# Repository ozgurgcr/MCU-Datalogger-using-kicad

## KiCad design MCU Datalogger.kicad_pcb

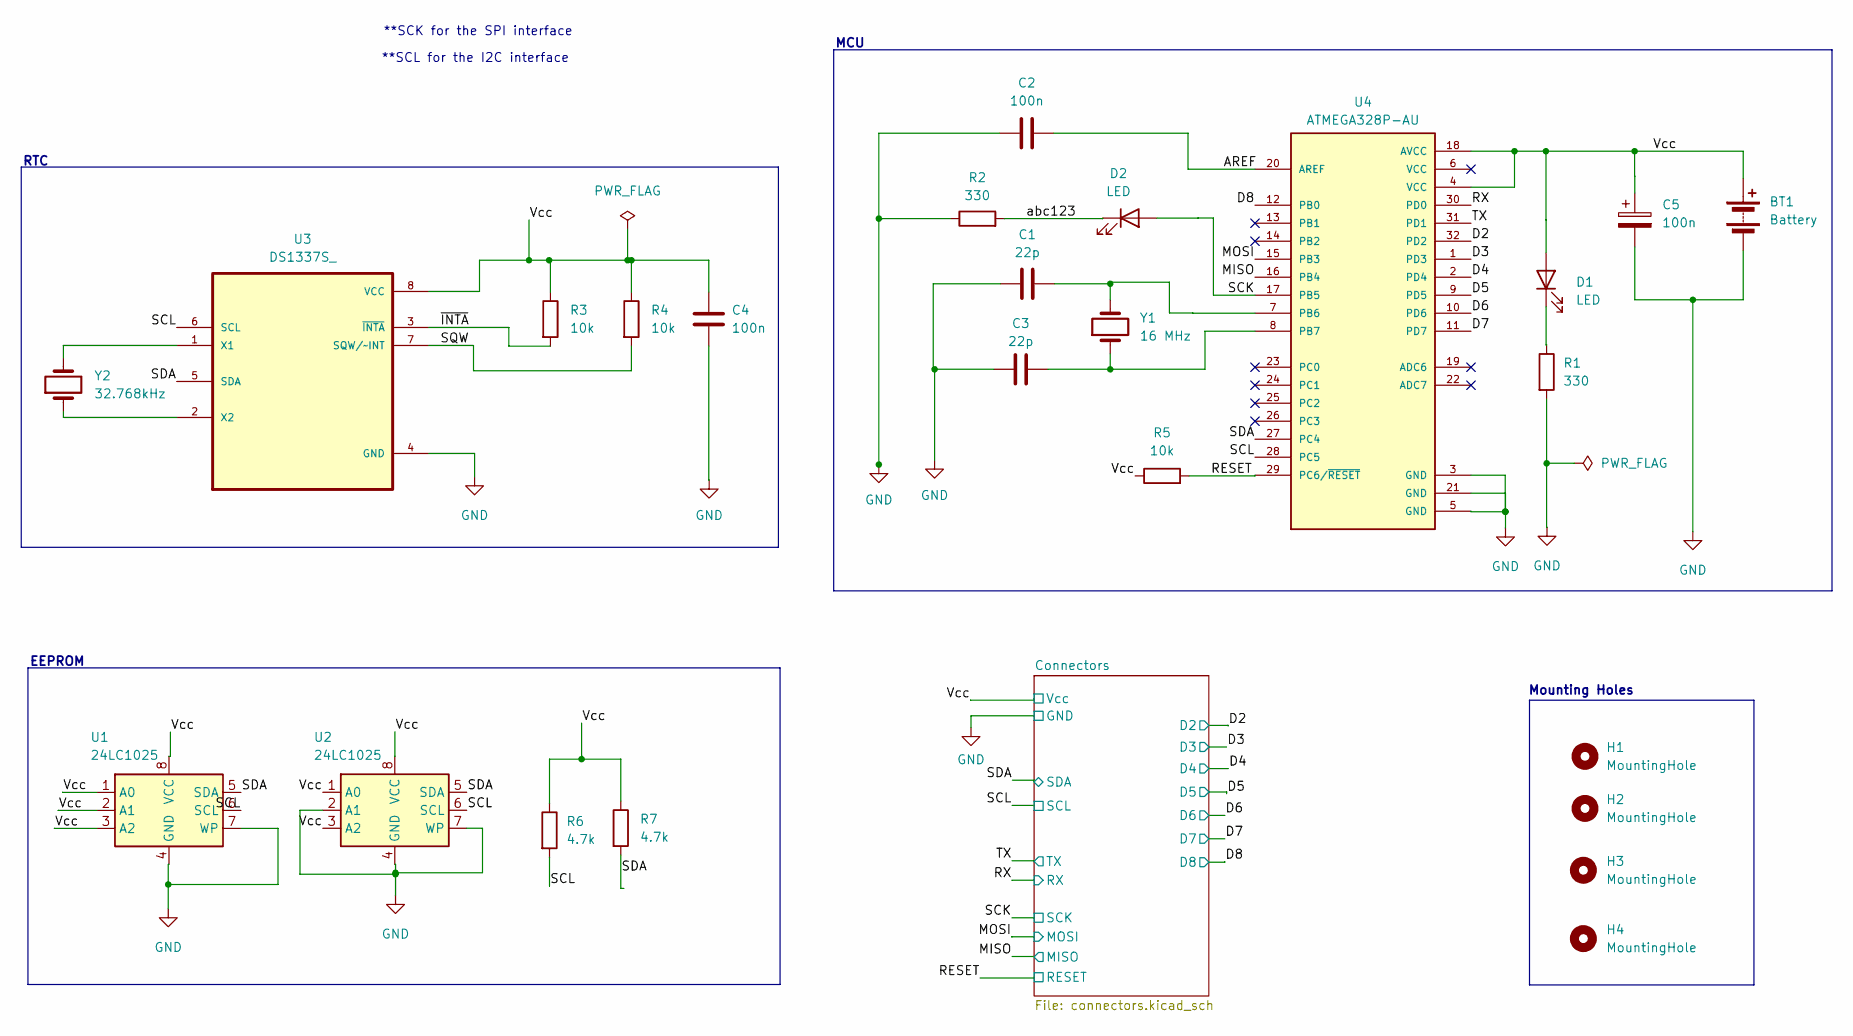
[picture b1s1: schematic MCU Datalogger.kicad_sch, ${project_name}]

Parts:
BT1: Battery; PinHeader_1x02_P2.54mm_Vertical
C1, C3: 22p; C_0805_2012Metric
C2, C4, C5: 100n; C_0805_2012Metric
D1, D2: LED; LED_0805_2012Metric
H1, H2, H3, H4: MountingHole; MountingHole_2.1mm
R1, R2: 330; R_0805_2012Metric
R3, R4, R5: 10k; R_0805_2012Metric
R6, R7: 4.7k; R_0805_2012Metric
U1, U2: 24LC1025; SOIC-8_5.23x5.23mm_P1.27mm
U3: DS1337S_; SOIC127P600X175-8N
U4: ATMEGA328P-AU; QFP80P900X900X120-32N; PARTREV 8271A
Y1: 16 MHz; Crystal_SMD_5032-2Pin_5.0x3.2mm_HandSoldering
Y2: 32.768kHz; Crystal_SMD_5032-2Pin_5.0x3.2mm_HandSoldering

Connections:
/AREF: C2.2, U4.20 (AREF)
/D2: U4.32 (PD2); also elsewhere on the board
/D3: U4.1 (PD3); also elsewhere on the board
/D4: U4.2 (PD4); also elsewhere on the board
/D5: U4.9 (PD5); also elsewhere on the board
/D6: U4.10 (PD6); also elsewhere on the board
/D7: U4.11 (PD7); also elsewhere on the board
/D8: U4.12 (PB0); also elsewhere on the board
/MISO: U4.16 (PB4); also elsewhere on the board
/MOSI: U4.15 (PB3); also elsewhere on the board
/RESET: R5.2, U4.29 (PC6/~RESET); also elsewhere on the board
/RX: U4.30 (PD0); also elsewhere on the board
/SCK: D2.2 (A), U4.17 (PB5); also elsewhere on the board
/SCL: R6.2, U1.6 (SCL), U2.6 (SCL), U3.6 (SCL), U4.28 (PC5); also elsewhere on the board
/SDA: R7.2, U1.5 (SDA), U2.5 (SDA), U3.5 (SDA), U4.27 (PC4); also elsewhere on the board
/SQW: R4.2, U3.7 (SQW/~INT)
/TX: U4.31 (PD1); also elsewhere on the board
/Vcc: BT1.1 (+), C4.2, C5.1, D1.2 (A), R3.1, R4.1, R5.1, R6.1, R7.1, U1.1 (A0), U1.2 (A1), U1.3 (A2), U1.8 (VCC), U2.1 (A0), U2.3 (A2), U2.8 (VCC), U3.8 (VCC), U4.4 (VCC), U4.18 (AVCC); also elsewhere on the board
/abc123: D2.1 (K), R2.2
/~INTA: R3.2, U3.3 (~INTA)
GND: BT1.2 (-), C1.1, C2.1, C3.1, C4.1, C5.2, R1.2, R2.1, U1.4 (GND), U1.7 (WP), U2.2 (A1), U2.4 (GND), U2.7 (WP), U3.4 (GND), U4.3 (GND), U4.5 (GND), U4.21 (GND); also elsewhere on the board
unnamed: D1.1 (K), R1.1
unnamed: U3.1 (X1), Y2.2
unnamed: U3.2 (X2), Y2.1
unnamed: C1.2, U4.7 (PB6), Y1.2
unnamed: C3.2, U4.8 (PB7), Y1.1

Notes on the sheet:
MCU
**SCL for the I2C interface
RTC
**SCK for the SPI interface
EEPROM
Mounting Holes

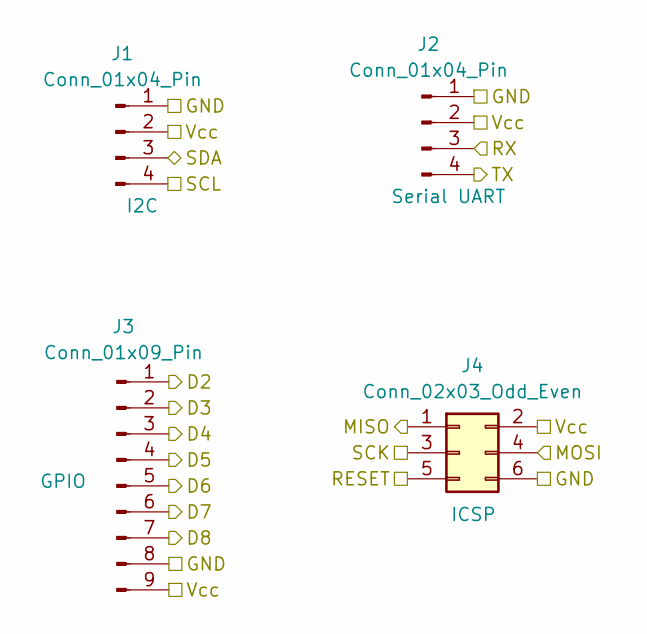
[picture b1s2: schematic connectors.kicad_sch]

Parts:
J1, J2: Conn_01x04_Pin; PinHeader_1x04_P2.54mm_Vertical
J3: Conn_01x09_Pin; PinHeader_1x09_P2.54mm_Vertical
J4: Conn_02x03_Odd_Even; PinHeader_2x03_P2.54mm_Vertical

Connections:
/D2: J3.1; also elsewhere on the board
/D3: J3.2; also elsewhere on the board
/D4: J3.3; also elsewhere on the board
/D5: J3.4; also elsewhere on the board
/D6: J3.5; also elsewhere on the board
/D7: J3.6; also elsewhere on the board
/D8: J3.7; also elsewhere on the board
/MISO: J4.1; also elsewhere on the board
/MOSI: J4.4; also elsewhere on the board
/RESET: J4.5; also elsewhere on the board
/RX: J2.3; also elsewhere on the board
/SCK: J4.3; also elsewhere on the board
/SCL: J1.4; also elsewhere on the board
/SDA: J1.3; also elsewhere on the board
/TX: J2.4; also elsewhere on the board
/Vcc: J1.2, J2.2, J3.9, J4.2; also elsewhere on the board
GND: J1.1, J2.1, J3.8, J4.6; also elsewhere on the board

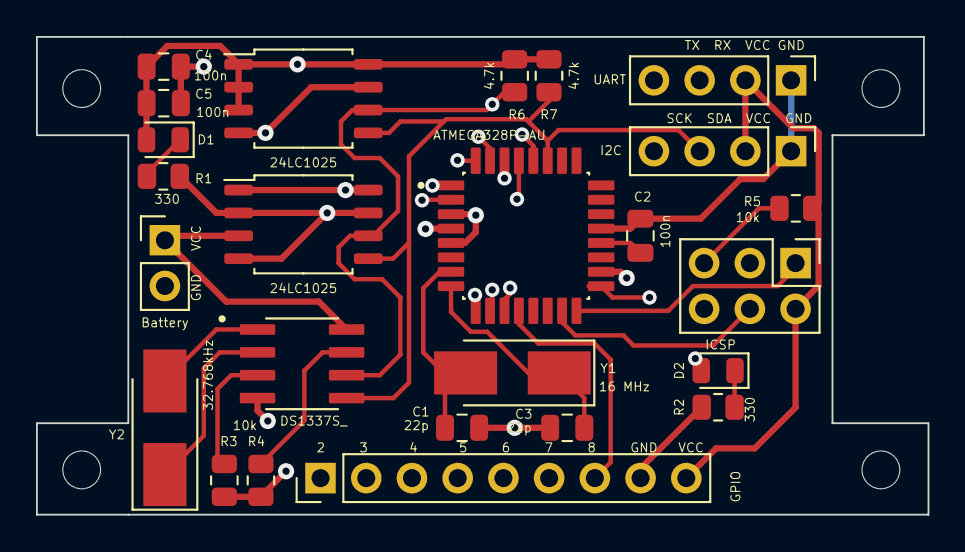
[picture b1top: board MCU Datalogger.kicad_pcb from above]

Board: 4 copper layers, 49.5 x 26.5 mm, 29 parts (0 on the bottom side), 26 nets.

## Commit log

2024-06-04 First commit of new project.
2024-06-05 Setup of EEschema for project
2024-06-05 Have added required symbols to schematic
2024-06-05 changed locations of symmbols (arrange)
2024-06-05 Added component values
2024-06-05 completed symbol to footprint assocciations
2024-06-05 completed wiring of main sheet
2024-06-05 Completed wiring in schematic
2024-06-05 allocated GND and Vcc nets to power net class
2024-06-05 Added auxilary comments and graphics for better documenting
2024-06-05 Setup pcbnew
2024-06-06 completed placement of footprints
2024-06-06 Routing completed, PWR zones added, DRC checked
2024-06-06 Silkscreen texts added and adjusted
2024-06-06 Logos and informations added
2024-06-06 Completed 2-laye PCB project
2024-06-06 Completed 2-layer PCB
2024-06-07 Added gerber directories in to the .gitignore
2024-06-07 4-layer PCB completed
2024-06-07 board charasteristics added
2024-06-07 Added gitattributes file to ignore files duirng merge
2024-06-07 gittatribute added
2024-06-07 Small changes made in schematic, added abc123 label, on branch main
2024-06-07 abc123 label fixed
2024-06-07 Clock bug detected
2024-06-07 Fixed two defects in the schematic
2024-06-07 gitignore updated
2024-06-07 Fixed 2 layer PCB clock issues
2024-06-07 Fixed net bugs in 4 layer PCB
